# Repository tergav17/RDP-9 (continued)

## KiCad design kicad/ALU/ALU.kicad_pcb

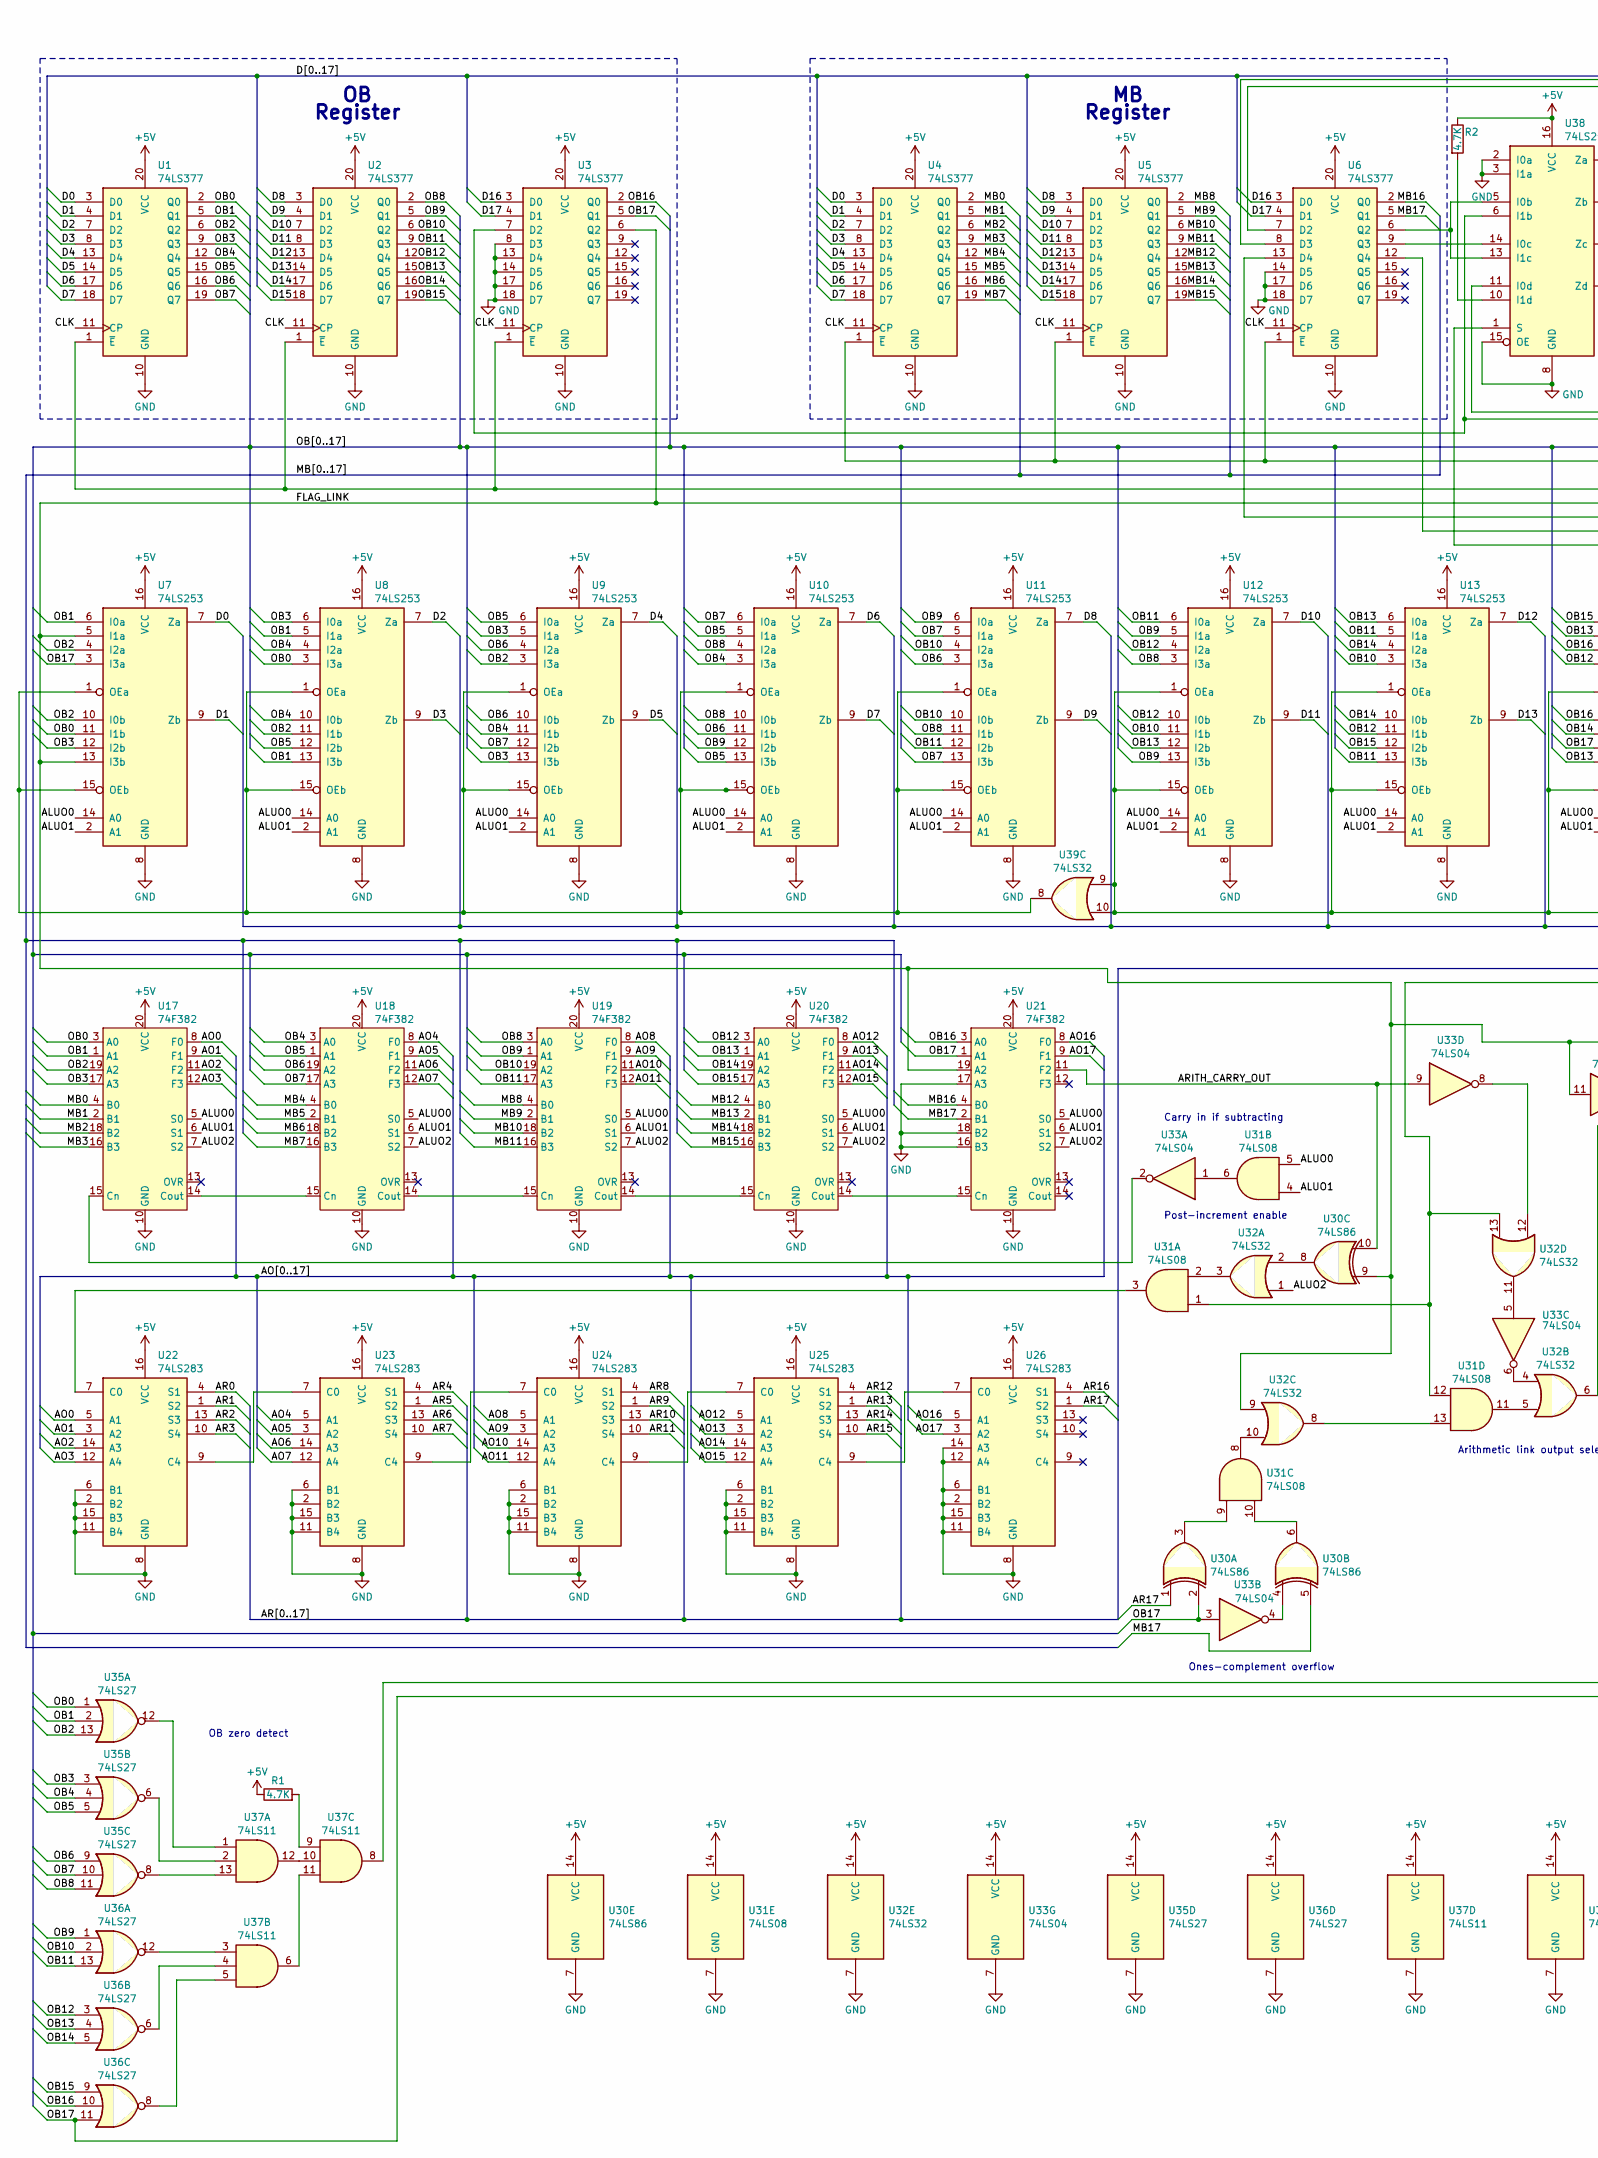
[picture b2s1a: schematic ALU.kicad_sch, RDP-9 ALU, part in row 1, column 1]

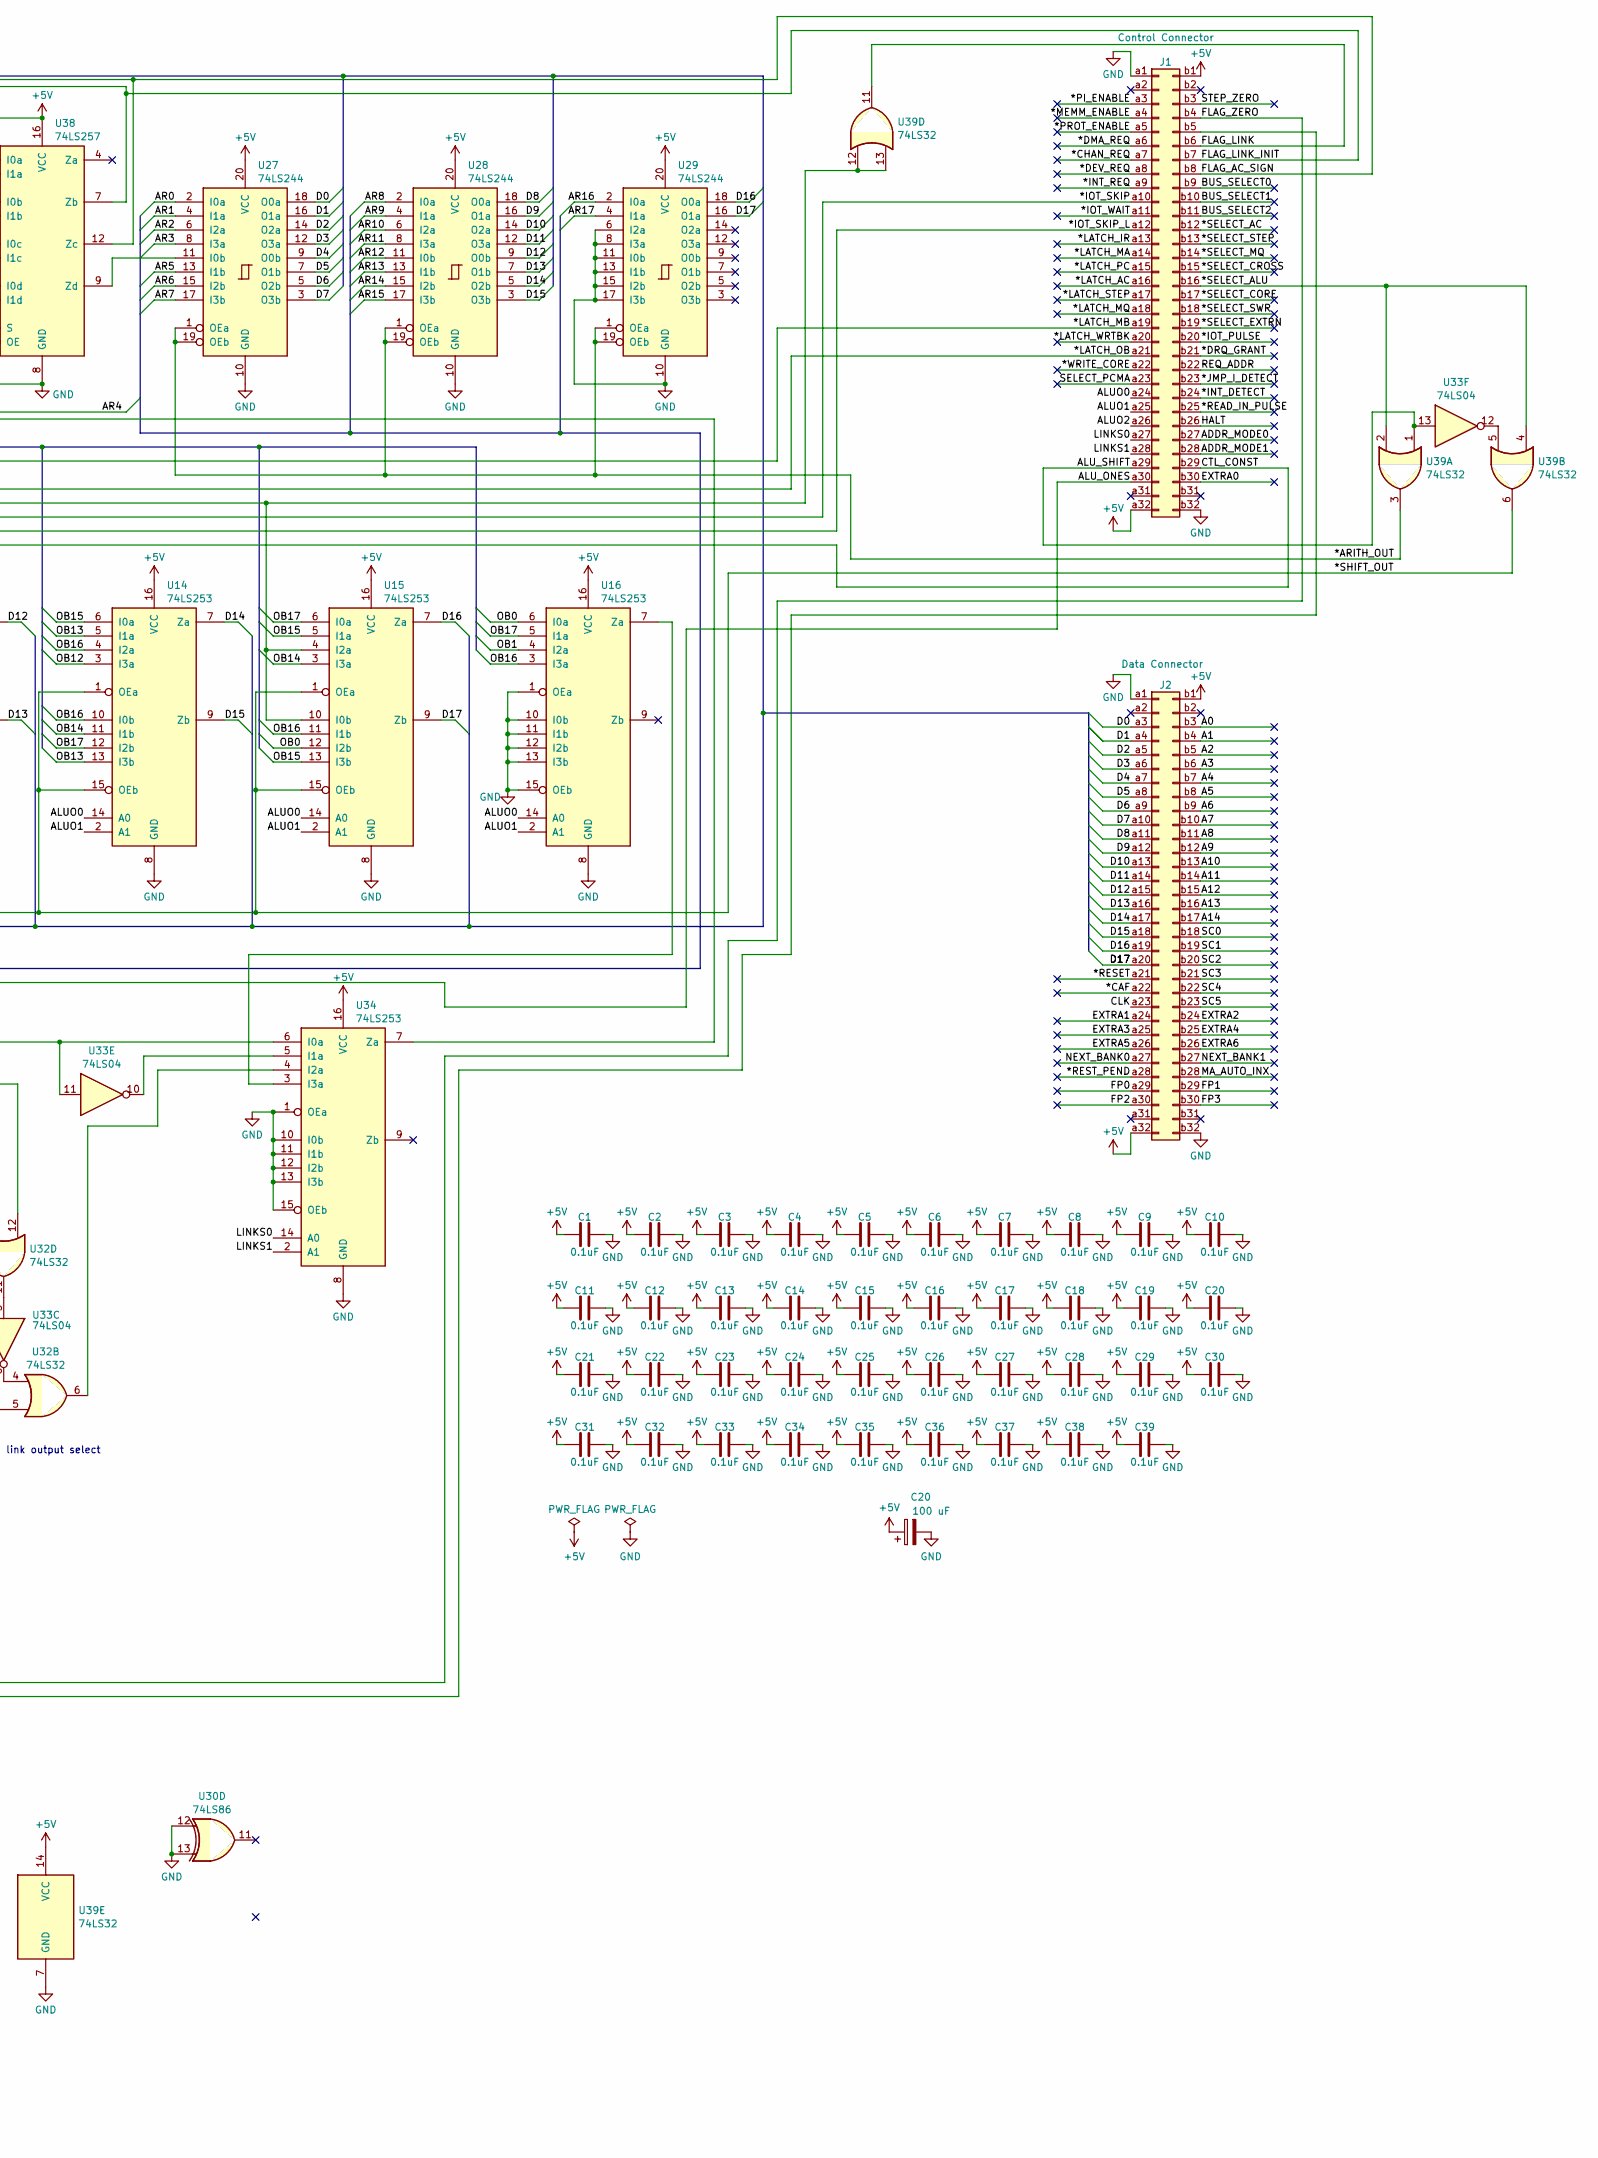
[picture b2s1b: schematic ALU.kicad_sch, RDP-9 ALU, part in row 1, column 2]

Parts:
C1, C2, C3, C4, C5, C6, C7, C8, C9, C10, C11, C12, C13, C14, C15, C16, C17, C18, C19, C21, C22, C23, C24, C25, C26, C27, C28, C29, C30, C31, C32, C33, C34, C35, C36, C37, C38, C39: 0.1uF; C_Disc_D5.0mm_W2.5mm_P5.00mm
C20: 100 uF; CP_Radial_D6.3mm_P2.50mm
J1: Control Connector; DIN41612_B_2x32_Male_Horizontal_THT
J2: Data Connector; DIN41612_B_2x32_Male_Horizontal_THT
R1, R2: 4.7K; R_Axial_DIN0207_L6.3mm_D2.5mm_P7.62mm_Horizontal
U1, U2, U3, U4, U5, U6: 74LS377; DIP-20_W7.62mm
U7, U8, U9, U10, U11, U12, U13, U14, U15, U16, U34: 74LS253; DIP-16_W7.62mm
U17, U18, U19, U20, U21: 74F382; DIP-20_W7.62mm
U22, U23, U24, U25, U26: 74LS283; DIP-16_W7.62mm
U27, U28, U29: 74LS244; DIP-20_W7.62mm
U30: 74LS86; DIP-14_W7.62mm
U31: 74LS08; DIP-14_W7.62mm
U32, U39: 74LS32; DIP-14_W7.62mm
U33: 74LS04; DIP-14_W7.62mm
U35, U36: 74LS27; DIP-14_W7.62mm
U37: 74LS11; DIP-14_W7.62mm
U38: 74LS257; DIP-16_W7.62mm

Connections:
+5V: C1.1, C2.1, C3.1, C4.1, C5.1, C6.1, C7.1, C8.1, C9.1, C10.1, C11.1, C12.1, C13.1, C14.1, C15.1, C16.1, C17.1, C18.1, C19.1, C20.1, C21.1, C22.1, C23.1, C24.1, C25.1, C26.1, C27.1, C28.1, C29.1, C30.1, C31.1, C32.1, C33.1, C34.1, C35.1, C36.1, C37.1, C38.1, C39.1, J1.a32, J1.b1, J2.a32, J2.b1, R1.1, R2.1, U1.20 (VCC), U2.20 (VCC), U3.20 (VCC), U4.20 (VCC), U5.20 (VCC), U6.20 (VCC), U7.16 (VCC), U8.16 (VCC), U9.16 (VCC), U10.16 (VCC), U11.16 (VCC), U12.16 (VCC), U13.16 (VCC), U14.16 (VCC), U15.16 (VCC), U16.16 (VCC), U17.20 (VCC), U18.20 (VCC), U19.20 (VCC), U20.20 (VCC), U21.20 (VCC), U22.16 (VCC), U23.16 (VCC), U24.16 (VCC), U25.16 (VCC), U26.16 (VCC), U27.20 (VCC), U28.20 (VCC), U29.20 (VCC), U30.14 (VCC), U31.14 (VCC), U32.14 (VCC), U33.14 (VCC), U34.16 (VCC), U35.14 (VCC), U36.14 (VCC), U37.14 (VCC), U38.16 (VCC), U39.14 (VCC); also elsewhere on the board
/*ARITH_OUT: U27.1 (OEa), U27.19 (OEb), U28.1 (OEa), U28.19 (OEb), U29.1 (OEa), U29.19 (OEb), U39.3
/*CAF: J2.a22
/*CHAN_REQ: J1.a7
/*DEV_REQ: J1.a8
/*DMA_REQ: J1.a6
/*DRQ_GRANT: J1.b21
/*INT_DETECT: J1.b24
/*INT_REQ: J1.a9
/*IOT_PULSE: J1.b20
/*IOT_SKIP: J1.a10, U6.13 (D4)
/*IOT_SKIP_L: J1.a12, U6.12 (Q4)
/*IOT_WAIT: J1.a11
/*JMP_I_DETECT: J1.b23
/*LATCH_AC: J1.a16
/*LATCH_IR: J1.a13
/*LATCH_MA: J1.a14
/*LATCH_MB: J1.a19, U4.1 (~E), U5.1 (~E), U6.1 (~E)
/*LATCH_MQ: J1.a18
/*LATCH_OB: J1.a21, U1.1 (~E), U2.1 (~E), U3.1 (~E)
/*LATCH_PC: J1.a15
/*LATCH_STEP: J1.a17
/*LATCH_WRTBK: J1.a20
/*MEMM_ENABLE: J1.a4
/*PI_ENABLE: J1.a3
/*PROT_ENABLE: J1.a5
/*READ_IN_PULSE: J1.b25
/*RESET: J2.a21
/*REST_PEND: J2.a28
/*SELECT_AC: J1.b12
/*SELECT_ALU: J1.b16, U39.2, U39.4
/*SELECT_CORE: J1.b17
/*SELECT_CROSS: J1.b15
/*SELECT_EXTRN: J1.b19
/*SELECT_MQ: J1.b14
/*SELECT_STEP: J1.b13
/*SELECT_SWR: J1.b18
/*SHIFT_OUT: U12.1 (OEa), U12.15 (OEb), U13.1 (OEa), U13.15 (OEb), U14.1 (OEa), U14.15 (OEb), U15.1 (OEa), U15.15 (OEb), U39.6, U39.9, U39.10
/*WRITE_CORE: J1.a22
/A0: J2.b3
/A1: J2.b4
/A2: J2.b5
/A3: J2.b6
/A4: J2.b7
/A5: J2.b8
/A6: J2.b9
/A7: J2.b10
/A8: J2.b11
/A9: J2.b12
/A10: J2.b13
/A11: J2.b14
/A12: J2.b15
/A13: J2.b16
/A14: J2.b17
/ADDR_MODE0: J1.b27
/ADDR_MODE1: J1.b28
/ALUO0: J1.a24, U7.14 (A0), U8.14 (A0), U9.14 (A0), U10.14 (A0), U11.14 (A0), U12.14 (A0), U13.14 (A0), U14.14 (A0), U15.14 (A0), U16.14 (A0), U17.5 (S0), U18.5 (S0), U19.5 (S0), U20.5 (S0), U21.5 (S0), U31.5
/ALUO1: J1.a25, U7.2 (A1), U8.2 (A1), U9.2 (A1), U10.2 (A1), U11.2 (A1), U12.2 (A1), U13.2 (A1), U14.2 (A1), U15.2 (A1), U16.2 (A1), U17.6 (S1), U18.6 (S1), U19.6 (S1), U20.6 (S1), U21.6 (S1), U31.4
/ALUO2: J1.a26, U17.7 (S2), U18.7 (S2), U19.7 (S2), U20.7 (S2), U21.7 (S2), U32.1
/ALU_ONES: J1.a30, U31.1, U31.12, U32.13
/ALU_SHIFT: J1.a29, U33.13, U39.1
/AO0: U17.8 (F0), U22.5 (A1)
/AO1: U17.9 (F1), U22.3 (A2)
/AO2: U17.11 (F2), U22.14 (A3)
/AO3: U17.12 (F3), U22.12 (A4)
/AO4: U18.8 (F0), U23.5 (A1)
/AO5: U18.9 (F1), U23.3 (A2)
/AO6: U18.11 (F2), U23.14 (A3)
/AO7: U18.12 (F3), U23.12 (A4)
/AO8: U19.8 (F0), U24.5 (A1)
/AO9: U19.9 (F1), U24.3 (A2)
/AO10: U19.11 (F2), U24.14 (A3)
/AO11: U19.12 (F3), U24.12 (A4)
/AO12: U20.8 (F0), U25.5 (A1)
/AO13: U20.9 (F1), U25.3 (A2)
/AO14: U20.11 (F2), U25.14 (A3)
/AO15: U20.12 (F3), U25.12 (A4)
/AO16: U21.8 (F0), U26.5 (A1)
/AO17: U21.9 (F1), U26.3 (A2)
/AR0: U22.4 (S1), U27.2 (I0a)
/AR1: U22.1 (S2), U27.4 (I1a)
/AR2: U22.13 (S3), U27.6 (I2a)
/AR3: U22.10 (S4), U27.8 (I3a)
/AR4: U23.4 (S1), U38.11 (I0d)
/AR5: U23.1 (S2), U27.13 (I1b)
/AR6: U23.13 (S3), U27.15 (I2b)
/AR7: U23.10 (S4), U27.17 (I3b)
/AR8: U24.4 (S1), U28.2 (I0a)
/AR9: U24.1 (S2), U28.4 (I1a)
/AR10: U24.13 (S3), U28.6 (I2a)
/AR11: U24.10 (S4), U28.8 (I3a)
/AR12: U25.4 (S1), U28.11 (I0b)
/AR13: U25.1 (S2), U28.13 (I1b)
/AR14: U25.13 (S3), U28.15 (I2b)
/AR15: U25.10 (S4), U28.17 (I3b)
/AR16: U26.4 (S1), U29.2 (I0a)
/AR17: U26.1 (S2), U29.4 (I1a), U30.1
/ARITH_CARRY_OUT: U21.11 (F2), U30.10, U33.9
/BUS_SELECT0: J1.b9
/BUS_SELECT1: J1.b10
/BUS_SELECT2: J1.b11
/CLK: J2.a23, U1.11 (CP), U2.11 (CP), U3.11 (CP), U4.11 (CP), U5.11 (CP), U6.11 (CP)
/CTL_CONST: J1.b29, U38.1 (S)
/D0: J2.a3, U1.3 (D0), U4.3 (D0), U7.7 (Za), U27.18 (O0a)
/D1: J2.a4, U1.4 (D1), U4.4 (D1), U7.9 (Zb), U27.16 (O1a)
/D2: J2.a5, U1.7 (D2), U4.7 (D2), U8.7 (Za), U27.14 (O2a)
/D3: J2.a6, U1.8 (D3), U4.8 (D3), U8.9 (Zb), U27.12 (O3a)
/D4: J2.a7, U1.13 (D4), U4.13 (D4), U9.7 (Za), U27.9 (O0b)
/D5: J2.a8, U1.14 (D5), U4.14 (D5), U9.9 (Zb), U27.7 (O1b)
/D6: J2.a9, U1.17 (D6), U4.17 (D6), U10.7 (Za), U27.5 (O2b)
/D7: J2.a10, U1.18 (D7), U4.18 (D7), U10.9 (Zb), U27.3 (O3b)
/D8: J2.a11, U2.3 (D0), U5.3 (D0), U11.7 (Za), U28.18 (O0a)
/D9: J2.a12, U2.4 (D1), U5.4 (D1), U11.9 (Zb), U28.16 (O1a)
/D10: J2.a13, U2.7 (D2), U5.7 (D2), U12.7 (Za), U28.14 (O2a)
/D11: J2.a14, U2.8 (D3), U5.8 (D3), U12.9 (Zb), U28.12 (O3a)
/D12: J2.a15, U2.13 (D4), U5.13 (D4), U13.7 (Za), U28.9 (O0b)
/D13: J2.a16, U2.14 (D5), U5.14 (D5), U13.9 (Zb), U28.7 (O1b)
/D14: J2.a17, U2.17 (D6), U5.17 (D6), U14.7 (Za), U28.5 (O2b)
/D15: J2.a18, U2.18 (D7), U5.18 (D7), U14.9 (Zb), U28.3 (O3b)
/D16: J2.a19, U3.3 (D0), U6.3 (D0), U15.7 (Za), U29.18 (O0a)
/D17: J2.a20, U3.4 (D1), U6.4 (D1), U15.9 (Zb), U29.16 (O1a)
/EXTRA0: J1.b30
/EXTRA1: J2.a24
/EXTRA2: J2.b24
/EXTRA3: J2.a25
/EXTRA4: J2.b25
/EXTRA5: J2.a26
/EXTRA6: J2.b26
/FLAG_AC_SIGN: J1.b8, U6.8 (D3), U38.12 (Zc)
/FLAG_LINK: J1.b6, U3.6 (Q2), U7.5 (I1a), U7.13 (I3b), U15.4 (I2a), U15.10 (I0b), U21.19 (A2), U30.9, U32.9, U33.11, U34.6 (I0a), U39.11, U39.12, U39.13
/FLAG_LINK_INIT: J1.b7, U6.7 (D2), U38.7 (Zb)
/FLAG_ZERO: J1.b4, U37.8
/FP0: J2.a29
/FP1: J2.b29
/FP2: J2.a30
/FP3: J2.b30
/HALT: J1.b26
/LINKS0: J1.a27, U34.14 (A0)
/LINKS1: J1.a28, U34.2 (A1)
/MA_AUTO_INX: J2.b28
/MB0: U4.2 (Q0), U17.4 (B0)
/MB1: U4.5 (Q1), U17.2 (B1)
/MB2: U4.6 (Q2), U17.18 (B2)
/MB3: U4.9 (Q3), U17.16 (B3)
/MB4: U4.12 (Q4), U18.4 (B0)
/MB5: U4.15 (Q5), U18.2 (B1)
/MB6: U4.16 (Q6), U18.18 (B2)
/MB7: U4.19 (Q7), U18.16 (B3)
/MB8: U5.2 (Q0), U19.4 (B0)
/MB9: U5.5 (Q1), U19.2 (B1)
/MB10: U5.6 (Q2), U19.18 (B2)
/MB11: U5.9 (Q3), U19.16 (B3)
/MB12: U5.12 (Q4), U20.4 (B0)
/MB13: U5.15 (Q5), U20.2 (B1)
/MB14: U5.16 (Q6), U20.18 (B2)
/MB15: U5.19 (Q7), U20.16 (B3)
/MB16: U6.2 (Q0), U21.4 (B0)
/MB17: U6.5 (Q1), U21.2 (B1), U30.5
/NEXT_BANK0: J2.a27
/NEXT_BANK1: J2.b27
/OB0: U1.2 (Q0), U7.11 (I1b), U8.3 (I3a), U15.12 (I2b), U16.6 (I0a), U17.3 (A0), U35.1
/OB1: U1.5 (Q1), U7.6 (I0a), U8.5 (I1a), U8.13 (I3b), U16.4 (I2a), U17.1 (A1), U35.2
/OB2: U1.6 (Q2), U7.4 (I2a), U7.10 (I0b), U8.11 (I1b), U9.3 (I3a), U17.19 (A2), U35.13
/OB3: U1.9 (Q3), U7.12 (I2b), U8.6 (I0a), U9.5 (I1a), U9.13 (I3b), U17.17 (A3), U35.3
/OB4: U1.12 (Q4), U8.4 (I2a), U8.10 (I0b), U9.11 (I1b), U10.3 (I3a), U18.3 (A0), U35.4
/OB5: U1.15 (Q5), U8.12 (I2b), U9.6 (I0a), U10.5 (I1a), U10.13 (I3b), U18.1 (A1), U35.5
/OB6: U1.16 (Q6), U9.4 (I2a), U9.10 (I0b), U10.11 (I1b), U11.3 (I3a), U18.19 (A2), U35.9
/OB7: U1.19 (Q7), U9.12 (I2b), U10.6 (I0a), U11.5 (I1a), U11.13 (I3b), U18.17 (A3), U35.10
/OB8: U2.2 (Q0), U10.4 (I2a), U10.10 (I0b), U11.11 (I1b), U12.3 (I3a), U19.3 (A0), U35.11
/OB9: U2.5 (Q1), U10.12 (I2b), U11.6 (I0a), U12.5 (I1a), U12.13 (I3b), U19.1 (A1), U36.1
/OB10: U2.6 (Q2), U11.4 (I2a), U11.10 (I0b), U12.11 (I1b), U13.3 (I3a), U19.19 (A2), U36.2
/OB11: U2.9 (Q3), U11.12 (I2b), U12.6 (I0a), U13.5 (I1a), U13.13 (I3b), U19.17 (A3), U36.13
/OB12: U2.12 (Q4), U12.4 (I2a), U12.10 (I0b), U13.11 (I1b), U14.3 (I3a), U20.3 (A0), U36.3
/OB13: U2.15 (Q5), U12.12 (I2b), U13.6 (I0a), U14.5 (I1a), U14.13 (I3b), U20.1 (A1), U36.4
/OB14: U2.16 (Q6), U13.4 (I2a), U13.10 (I0b), U14.11 (I1b), U15.3 (I3a), U20.19 (A2), U36.5
/OB15: U2.19 (Q7), U13.12 (I2b), U14.6 (I0a), U15.5 (I1a), U15.13 (I3b), U20.17 (A3), U36.9
/OB16: U3.2 (Q0), U14.4 (I2a), U14.10 (I0b), U15.11 (I1b), U16.3 (I3a), U21.3 (A0), U36.10
/OB17: J1.b5, U3.5 (Q1), U7.3 (I3a), U14.12 (I2b), U15.6 (I0a), U16.5 (I1a), U21.1 (A1), U30.2, U33.3, U36.11
/REQ_ADDR: J1.b22
/SC0: J2.b18
/SC1: J2.b19
/SC2: J2.b20
/SC3: J2.b21
/SC4: J2.b22
/SC5: J2.b23
/SELECT_PCMA: J1.a23
/STEP_ZERO: J1.b3
GND: C1.2, C2.2, C3.2, C4.2, C5.2, C6.2, C7.2, C8.2, C9.2, C10.2, C11.2, C12.2, C13.2, C14.2, C15.2, C16.2, C17.2, C18.2, C19.2, C20.2, C21.2, C22.2, C23.2, C24.2, C25.2, C26.2, C27.2, C28.2, C29.2, C30.2, C31.2, C32.2, C33.2, C34.2, C35.2, C36.2, C37.2, C38.2, C39.2, J1.a1, J1.b32, J2.a1, J2.b32, U1.10 (GND), U2.10 (GND), U3.8 (D3), U3.10 (GND), U3.13 (D4), U3.14 (D5), U3.17 (D6), U3.18 (D7), U4.10 (GND), U5.10 (GND), U6.10 (GND), U6.14 (D5), U6.17 (D6), U6.18 (D7), U7.8 (GND), U8.8 (GND), U9.8 (GND), U10.8 (GND), U11.8 (GND), U12.8 (GND), U13.8 (GND), U14.8 (GND), U15.8 (GND), U16.1 (OEa), U16.8 (GND), U16.10 (I0b), U16.11 (I1b), U16.12 (I2b), U16.13 (I3b), U16.15 (OEb), U17.10 (GND), U18.10 (GND), U19.10 (GND), U20.10 (GND), U21.10 (GND), U21.16 (B3), U21.17 (A3), U21.18 (B2), U22.2 (B2), U22.6 (B1), U22.8 (GND), U22.11 (B4), U22.15 (B3), U23.2 (B2), U23.6 (B1), U23.8 (GND), U23.11 (B4), U23.15 (B3), U24.2 (B2), U24.6 (B1), U24.8 (GND), U24.11 (B4), U24.15 (B3), U25.2 (B2), U25.6 (B1), U25.8 (GND), U25.11 (B4), U25.15 (B3), U26.2 (B2), U26.6 (B1), U26.8 (GND), U26.11 (B4), U26.12 (A4), U26.14 (A3), U26.15 (B3), U27.10 (GND), U28.10 (GND), U29.6 (I2a), U29.8 (I3a), U29.10 (GND), U29.11 (I0b), U29.13 (I1b), U29.15 (I2b), U29.17 (I3b), U30.7 (GND), U30.12, U30.13, U31.7 (GND), U32.7 (GND), U33.7 (GND), U34.1 (OEa), U34.8 (GND), U34.10 (I0b), U34.11 (I1b), U34.12 (I2b), U34.13 (I3b), U34.15 (OEb), U35.7 (GND), U36.7 (GND), U37.7 (GND), U38.2 (I0a), U38.3 (I1a), U38.8 (GND), U38.15 (OE), U39.7 (GND); also elsewhere on the board
unnamed: R1.2, U37.9
unnamed: U3.7 (D2), U34.7 (Za), U38.6 (I1b)
unnamed: U7.1 (OEa), U7.15 (OEb), U8.1 (OEa), U8.15 (OEb), U9.1 (OEa), U9.15 (OEb), U10.1 (OEa), U10.15 (OEb), U11.1 (OEa), U11.15 (OEb), U39.8
unnamed: U16.7 (Za), U34.3 (I3a)
unnamed: U17.15 (Cn), U33.2
unnamed: U17.14 (Cout), U18.15 (Cn)
unnamed: U18.14 (Cout), U19.15 (Cn)
unnamed: U19.14 (Cout), U20.15 (Cn)
unnamed: U20.14 (Cout), U21.15 (Cn)
unnamed: U22.7 (C0), U31.3
unnamed: U22.9 (C4), U23.7 (C0)
unnamed: U23.9 (C4), U24.7 (C0)
unnamed: U24.9 (C4), U25.7 (C0)
unnamed: U25.9 (C4), U26.7 (C0)
unnamed: U27.11 (I0b), U38.9 (Zd)
unnamed: U30.3, U31.9
unnamed: U30.4, U33.4
unnamed: U30.6, U31.10
unnamed: U30.8, U32.2
unnamed: U31.2, U32.3
unnamed: U31.6, U33.1
unnamed: U31.8, U32.10
unnamed: U31.11, U32.5
unnamed: U31.13, U32.8
unnamed: U32.4, U33.6
unnamed: U32.11, U33.5
unnamed: U32.12, U33.8
unnamed: U33.12, U39.5
unnamed: U33.10, U34.5 (I1a)
unnamed: U32.6, U34.4 (I2a)
unnamed: U35.6, U37.2
unnamed: U35.8, U37.13
unnamed: U35.12, U37.1
unnamed: U36.6, U37.4
unnamed: U36.8, U37.5
unnamed: U36.12, U37.3
unnamed: U37.10, U37.12
unnamed: U37.6, U37.11
unnamed: U6.6 (Q2), U38.5 (I0b), U38.13 (I1c)
unnamed: U6.9 (Q3), U38.14 (I0c)
unnamed: R2.2, U38.10 (I1d)

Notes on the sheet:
Carry in if subtracting
Arithmetic link output select
Register
OB zero detect
Post-increment enable
Ones-complement overflow

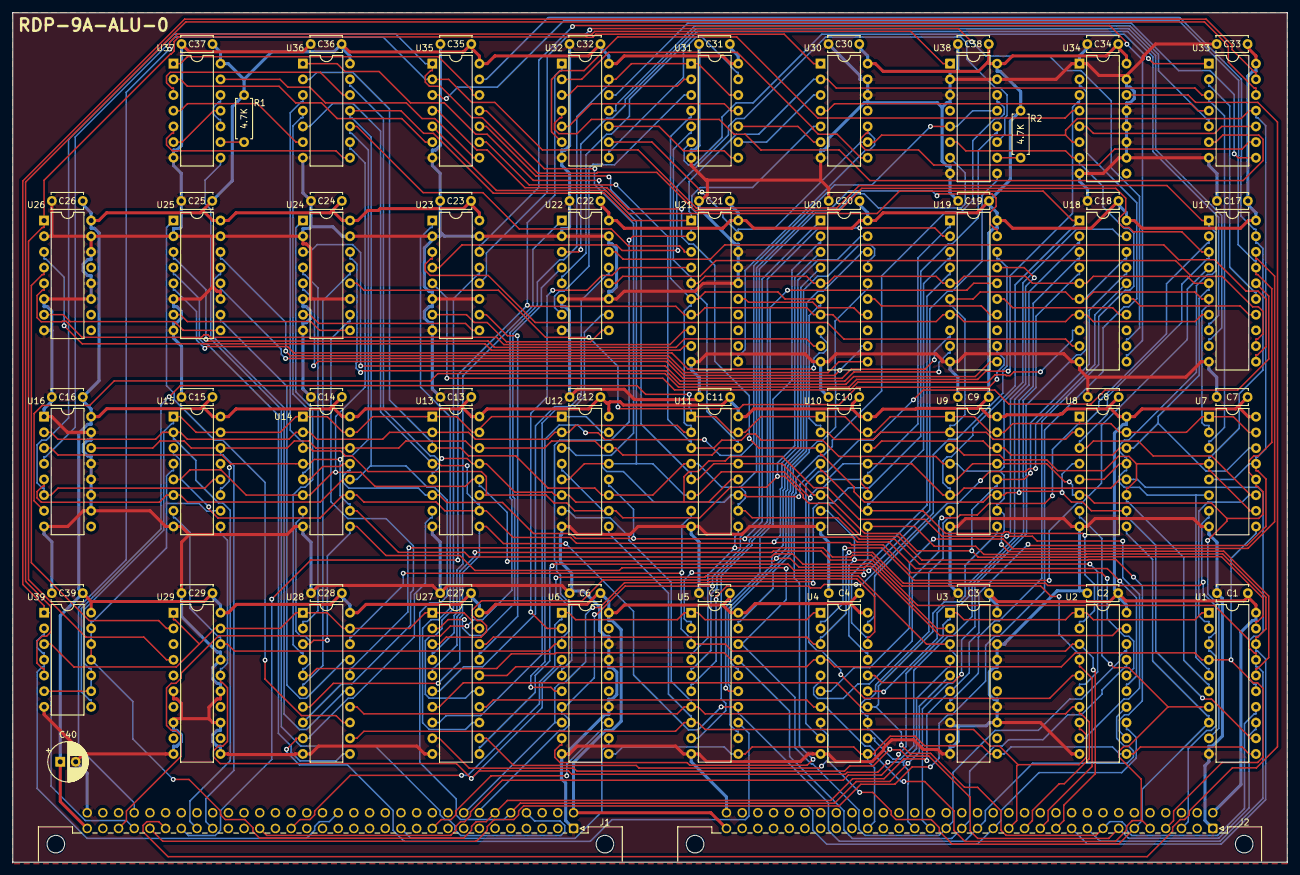
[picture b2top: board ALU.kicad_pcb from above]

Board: 2 copper layers, 206.4 x 137.5 mm, 83 parts (0 on the bottom side), 154 nets.

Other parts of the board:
C40: 100 uF; CP_Radial_D6.3mm_P2.50mm

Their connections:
+5V: C40.1; also elsewhere on the board
GND: C40.2; also elsewhere on the board
